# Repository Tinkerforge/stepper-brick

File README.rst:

Stepper Brick
=============

This repository contains the firmware source code and the hardware design
files. The documentation generator configs can be found at
https://github.com/Tinkerforge/generators

Repository Content
------------------

software/:
 * examples/: Examples for all supported languages
 * build/: Compiled files
 * src/: Source code of firmware
 * Makefile: Makefile to build project

hardware/:
 * Contains KiCad project files and additionally schematics as PDF

datasheets/:
 * Contains datasheets for sensors and complex ICs that are used

Hardware
--------

The hardware is designed with the open source EDA Suite KiCad
(http://www.kicad.org). Before you are able to open the files,
you have to install the Tinkerforge kicad-libraries
(https://github.com/Tinkerforge/kicad-libraries). You can either clone
them directly in hardware/ or clone them in a separate folder and
symlink them into hardware/
(ln -s kicad_path/kicad-libraries project_path/hardware). After that you
can open the .pro file in hardware/ with KiCad and from there view and
modify the schematics and the PCB layout.

Software
--------

If you want to do your own Brick/Bricklet firmware development we highly
recommend that you use our build environment setup script and read the
tutorial (https://www.tinkerforge.com/en/doc/Tutorials/Tutorial_Build_Environment/Tutorial.html).

To compile the C code we recommend you to install the newest GNU Arm Embedded
Toolchain (https://launchpad.net/gcc-arm-embedded/+download).
You also need to install bricklib (https://github.com/Tinkerforge/bricklib).

You can either clone it directly in software/src/ or clone it in a
separate folder and symlink it into software/src/
(ln -s bricklib_path/bricklib project_path/software/src/). Finally make sure to
have CMake installed (http://www.cmake.org/cmake/resources/software.html).

After that you can build the firmware by invoking make in software/.
The firmware (.bin) can then be found in software/build/ and uploaded
with brickv (click button "Flashing" on start screen).

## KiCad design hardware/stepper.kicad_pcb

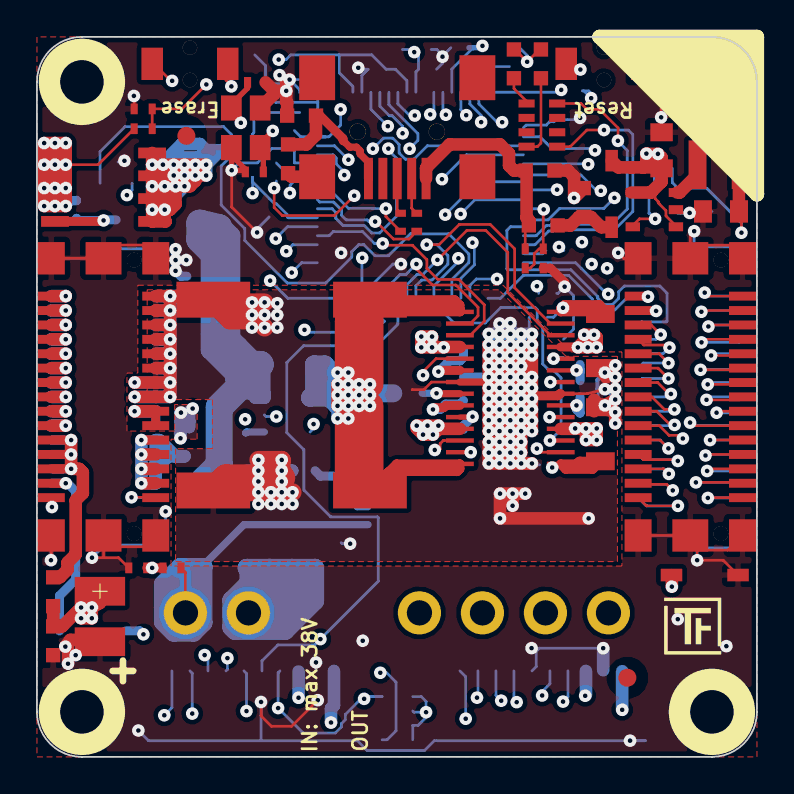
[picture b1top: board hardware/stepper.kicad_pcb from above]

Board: 4 copper layers, 40.0 x 40.0 mm, 107 parts (0 on the bottom side), 109 nets.

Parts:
C1, C2: 9pF; C0402
C3, C4, C5, C11, C14, C17, C20, C21, C22, C24, C25, C27, C28, C30, C32, C33: 100nF; C0402
C6, C8: 1nF; C0402
C7, C12, C13: 220nF; C0603
C9, C10: 330µF/50V; ELKO_103
C15: 100µF; 3528-21
C16, C18: 10µF; C0805
C19, C31: 4.7µF; C0603
C23: 2.2µF; C0603
C26: DNP; C0402
C29: 10µF/10V; C0805
C34, C35, C36: DNP; C0603
D1: blue; D0603
D2: red; D0603
D3: Z12V; SOD-123
D4, D5: PMEG4050BEP; SOD-128
D6, D7: B0520LW-7-F; SOD-123
D8: Z3.3V; SOD-123
FB1, FB2, FB3, FB4, FB5: FB; C0603
Fiducial_Mark: VAL**; Fiducial_Mark
Fiducial_Mark#2, Fiducial_Mark#3, Fiducial_Mark#4: VAL**; Fiducial_Mark
J1, J2, J3, J4: DRILL; DRILL_NP
J5: USB-MINI-B-SMD
J6, J8: STACK-UP-HIGH; BTB08-ACS-TOP
J7, J9: STACK-DOWN; BTB08-ACS-BTM
L1: NR3015T4R7M; NR3030
L2: LBR2012T100K; C0805
P1: black; OQ_2P
P2: green; OQ_4P
P3, P4: CON-SENSOR
Q1: FDS8449; SOIC-8-MOSFET
Q2: AO4421; SOIC-8-MOSFET
Q3: 2N7002; SOT23GDS
R1, R2: 27; R0402
R3: 1.8k; R0402
R4, R14: 2.7k; R0402
R5: FB; C0603
R6, R10, R12, R18: 10k; R0402
R7, R11, R13, R16, R22: 1k; R0402
R8: 10k; 0402
R9: 100k; R0402
R15, R19: 47k; R0402
R17: 0.01; R1206
R20, R21: 0.15; R1206
R23: 0; R0603
R24: DNP; R0603
R25: 1R0; R0402
RP1, RP2: 1k; 4X0603
SW1: Reset; TACT-SWITCH
SW2: Erase; TACT-SWITCH
U1: AT91SAM3SXB; LQFP64
U2: ZXCT1086; SOT23-5
U3: DRV8811PWP; HTSSOP28
U4: EUP3406; SOT23-5
VAL: WEEE_7mm
VAL#2: CE_5mm
X1: 16Mhz; CRYSTAL_3225

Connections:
3V3: C5.2, C16.1, C17.1, C19.1, C20.1, C21.1, C22.1, C26.1, C29.1, C30.1, C33.1, D1.1, D2.1, D6.1, D8.2, J6.20, L1.2, P3.3, P3.6, P4.3, R16.1, R23.1, RP2.1, RP2.2, RP2.3, RP2.4, SW2.2, U1.1, U1.7, U1.18, U1.45, U1.58, U2.5, U3.10
BRICKLET-I2C-SCL: P3.4, P4.4, RP2.5, U1.36
BRICKLET-I2C-SDA: P3.5, P4.5, RP2.8, U1.43
BRICKLET-IO0_0/AD0: P3.7, U1.3
BRICKLET-IO0_1: P3.8, U1.5
BRICKLET-IO0_2/PWM0: P3.9, U1.48
BRICKLET-IO0_3: P3.10, U1.25
BRICKLET-IO1_0/AD1: P4.7, U1.4
BRICKLET-IO1_1: P4.8, U1.6
BRICKLET-IO1_2/PWM1: P4.9, U1.47
BRICKLET-IO1_3: P4.10, U1.19
GND: C1.2, C2.2, C3.2, C4.2, C5.1, C15.2, C16.2, C17.2, C18.2, C19.2, C20.2, C21.2, C22.2, C23.2, C24.2, C25.2, C27.2, C28.2, C29.2, C30.2, C31.2, C32.2, C33.2, C34.2, C35.2, C36.2, D8.1, FB1.1, FB4.2, J6.EP, J7.EP, J8.EP, J9.EP, P3.2, P3.EP, P4.2, P4.6, P4.EP, R4.1, R5.2, R7.2, R11.2, R13.1, R24.2, SW1.2, U1.2, U1.17, U1.46, U1.60, U2.2, U4.2, X1.3
unnamed: C3.1, R12.1, R14.2, U3.8
unnamed: C6.1, R15.1, U3.6
unnamed: C7.2, U3.20
unnamed: C8.1, R19.1, U3.9
unnamed: C11.2, R20.1, U3.14
unnamed: C12.1, U3.23
unnamed: C12.2, U3.24
unnamed: C13.2, U3.22
unnamed: C14.1, R21.2, U3.1
unnamed: C23.1, C24.1, C25.1, C27.1, C28.1, L2.1, U1.8, U1.12, U1.24, U1.54
unnamed: C26.2, R23.2, R24.1, U4.5
unnamed: C31.1, R25.1
unnamed: C32.1, L2.2, R25.2, U1.64
unnamed: C35.1, FB3.2, J5.1, R3.1
unnamed: D1.2, RP1.1
unnamed: D2.2, RP1.4
unnamed: D3.2, Q1.G, R9.2
unnamed: D4.1, Q2.D
unnamed: D4.2, D5.2, R17.2, U2.3
unnamed: D5.1, P1.1, R9.1, R10.1
unnamed: D6.2, J8.28, J9.28
unnamed: FB1.2, FB2.1, J5.5
unnamed: FB2.2, J5.6
unnamed: FB4.1, J8.21, J8.23, J8.25, J8.27, J9.21, J9.23, J9.25, J9.27
unnamed: FB5.2, J8.22, J8.24, J8.26, J9.22, J9.24, J9.26
unnamed: J5.2, R1.1
unnamed: J5.3, R2.1
unnamed: J6.6, J7.8
unnamed: J6.7, J7.7, R22.1
unnamed: J6.8, J7.10
unnamed: J6.10, J7.12
unnamed: J6.12, J7.14
unnamed: J6.13, J7.13
unnamed: J6.14, J7.16
unnamed: J6.15, J7.15
unnamed: J6.16, J7.18
unnamed: J6.17, J7.17
unnamed: J6.18, J7.20
unnamed: J6.21, J7.21
unnamed: J6.22, J7.22
unnamed: J6.23, J7.23
unnamed: J6.24, J7.24
unnamed: J6.25, J7.25
unnamed: J6.27, J7.27
unnamed: J6.29, J7.29
unnamed: J6.30, J7.30
unnamed: J8.29, J9.29
unnamed: J8.30, J9.30
unnamed: L1.1, U4.3
unnamed: P1.2, Q1.D
unnamed: P2.1, U3.25
unnamed: P2.2, U3.4
unnamed: P2.3, U3.18
unnamed: P2.4, U3.11
unnamed: Q2.G, Q3.D, R8.1
unnamed: R1.2, U1.56
unnamed: R2.2, U1.57
unnamed: R18.2, U2.1
unnamed: RP1.5, U1.29
unnamed: RP1.8, U1.30
unnamed: SW2.1, U1.55
PWR-CUR-SENSE: R18.1, U1.10
PWR-DAC-1/5: R14.1, U1.31
PWR-DAC-DECAY: C4.1, U1.63, U3.5
PWR-DAC-VREF: R12.2, U1.59
PWR-DIR: U1.38, U3.3
PWR-ENABLE: R16.2, U1.15, U3.26
PWR-HOME: U1.35, U3.2
PWR-RESET: U1.52, U3.17
PWR-SLEEP: U1.23, U3.27
PWR-SR: U1.44, U3.16
PWR-STEP: U1.20, U3.19
PWR-USM0: U1.41, U3.13
PWR-USM1: U1.42, U3.12
PWR-VEXT: R10.2, R11.1, U1.13
PWR-VSTACK: R6.2, R7.1, U1.16
PWR-VSTACK-SW: Q3.G, R13.2, U1.37
STACK-DETECT/JTAG-TMS: J6.9, J7.9, U1.51
STACK-I2C-SCL/JTAG-TDO: J6.4, J7.4, U1.49
STACK-I2C-SDA/JTAG-TDI: J6.2, J7.2, U1.33
STACK-INT: J6.19, J7.19, U1.32
STACK-PGND: C6.2, C7.1, C8.2, C9.2, C10.2, C11.1, C14.2, D3.1, J8.1, J8.3, J8.5, J8.7, J8.9, J8.11, J8.13, J8.15, J8.17, J8.19, J9.1, J9.3, J9.5, J9.7, J9.9, J9.11, J9.13, J9.15, J9.17, J9.19, Q1.S, Q3.S, R5.1, R15.2, R19.2, R20.2, R21.1, U3.7, U3.21, U3.EP
STACK-PVCC: J8.2, J8.4, J8.6, J8.8, J8.10, J8.12, J8.14, J8.16, J8.18, J8.20, J9.2, J9.4, J9.6, J9.8, J9.10, J9.12, J9.14, J9.16, J9.18, J9.20, Q2.S, R6.1, R8.2
STACK-RESET: R22.2, SW1.1, U1.39
STACK-SER-RXD: J6.26, J7.26, U1.11
STACK-SER-TXD: J6.28, J7.28, U1.14
STACK-SPI-MISO: J6.1, J7.1, U1.27
STACK-SPI-MOSI: J6.3, J7.3, U1.22
STACK-SPI-SCLK: J6.5, J7.5, U1.21
STACK-SPI-SELECT: J7.6, U1.28
STACK-SYNC/JTAG-TCK: J6.11, J7.11, U1.53
USB-DETECT: R3.2, R4.2, U1.26
VPP: C9.1, C10.1, C13.1, R17.1, U2.4, U3.15, U3.28
VSTACK: C15.1, C18.1, C36.1, D7.2, FB5.1, P3.1, P4.1, U4.1, U4.4
VUSB: C34.1, D7.1, FB3.1
XIN: C2.1, U1.62, X1.2
XOUT: C1.1, U1.61, X1.1

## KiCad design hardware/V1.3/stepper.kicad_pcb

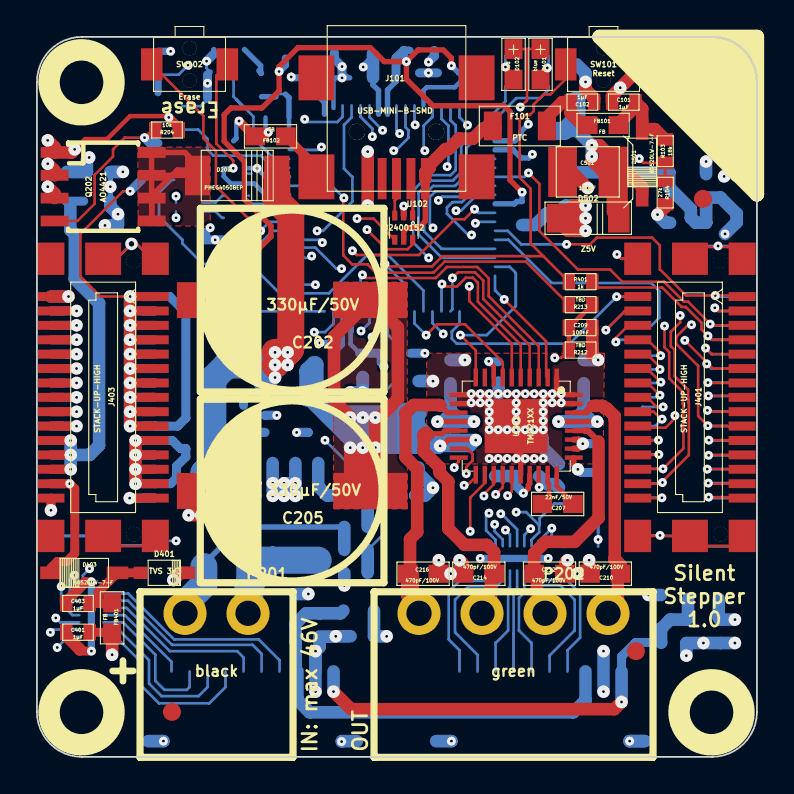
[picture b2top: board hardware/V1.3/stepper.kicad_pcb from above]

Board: 4 copper layers, 40.0 x 40.0 mm, 127 parts (0 on the bottom side), 128 nets.

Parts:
C101, C102, C301, C302, C303, C304, C401, C402, C403, C404: 1µF; 0402E
C103, C104: 9pF; 0402E
C201, C209, C217, C218, C503, C506, C507, C508, C510, C511, C512, C513, C515, C517, C518: 100nF; 0402E
C202, C205: 330µF/50V; ELKO_103
C203: 470nF; 0402E
C204, C505, C516: 4.7µF; 0603E
C206, C208, C211, C213: 100nF/50V; 0603E
C207: 22nF/50V; 0603E
C210, C212, C214, C216: 470pF/100V; 0603E
C215: 4.7µF/50V; 1206
C501: 100µF; 3528-21
C502, C504: 10µF; 0805
C509: 2.2µF; 0603E
C514: 10µF/10V; 0805
D101: blue; D0603E
D102: red; D0603E
D201: Z12V; SOD-123
D202, D203: PMEG4050BEP; SOD-128
D301, D402: ESD5V0D3B-TP; SOD-323
D302: ESD3V3D3B-TP; SOD-323
D401: TVS 3V3; SOD-323
D403, D501: B0520LW-7-F; SOD-123
D502: Z5V; MiniMelf
D503: Z3.3V; MiniMelf
F101: PTC; 1206
FB101, FB102, FB401, FB402: FB; 0603E
FB301, FB302: FILTER; 0603E
FILTER301, FILTER302: Filter-8x; DFN16-33x135
Fiducial_Mark: VAL**; Fiducial_Mark
Fiducial_Mark#2, Fiducial_Mark#3, Fiducial_Mark#4, Fiducial_Mark#5, Fiducial_Mark#6: VAL**; Fiducial_Mark
J101: USB-MINI-B-SMD
J102, J103, J104, J105: DRILL; DRILL_NP
J401, J403: STACK-UP-HIGH; BTB08-ACS-TOP
J402, J404: STACK-DOWN; BTB08-ACS-BTM
L101: 744230900; WE-CNSW-0603
L501: LBR2012T100K; 0805
P201: black; OQ_2P
P202: green; OQ_4P
P301, P302: CON-SENSOR
Q201: FDS8449; SOIC-8-MOSFET
Q202: AO4421; SOIC-8-MOSFET
Q203: 2N7002; SOT23GDS
R101, R102: 27; 0402E
R103: 18k; 0402E
R104: 27k; 0402E
R201: 0; 0603E
R202, R204, R206, R210: 10k; 0402E
R203, R207, R208, R401: 1k; 0402E
R205: 100k; 0402E
R209: 0.01; 1206
R211: 2R2; 0402E
R212, R213: TBD; 0402E
R214, R215: 0.12/0.5W; 1206
R501: 1R0; 0402E
RP101, RP301: 1k; 4X0603
SW101: Reset; TACT-SWITCH
SW102: Erase; TACT-SWITCH
U101: AT91SAM3SXB; LQFP64
U102: 82400152; SOT563-SPEC
U201: ZXCT1086; SOT23-5
U202: TMC21XX; QFN36_5X6
U501: LD1117; SOT-223
VAL: WEEE_7mm_back
VAL#2: CE_5mm
X101: 16Mhz; CRYSTAL_3225

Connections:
3V3: C201.2, C302.1, C401.1, C502.1, C503.1, C505.1, C506.1, C507.1, C508.1, C514.1, C515.1, C518.1, D101.1, D102.1, D503.2, FB302.1, FB401.1, FILTER302.14, J401.20, RP301.1, RP301.2, RP301.3, RP301.4, SW102.2, U101.1, U101.7, U101.18, U101.45, U101.58, U201.5, U202.8, U501.2
BRICKLET-I2C-SCL: FILTER301.16, FILTER302.16, RP301.8, U101.36
BRICKLET-I2C-SDA: FILTER301.15, FILTER302.15, RP301.5, U101.43
BRICKLET-IO0_0/AD0: FILTER301.10, U101.3
BRICKLET-IO0_1: FILTER301.11, U101.5
BRICKLET-IO0_2/PWM0: FILTER301.12, U101.48
BRICKLET-IO0_3: FILTER301.13, U101.25
BRICKLET-IO1_0/AD1: FILTER302.13, U101.4
BRICKLET-IO1_1: FILTER302.12, U101.6
BRICKLET-IO1_2/PWM1: FILTER302.11, U101.47
BRICKLET-IO1_3: FILTER302.10, U101.19
GND: C101.2, C102.2, C103.2, C104.2, C301.2, C302.2, C303.2, C304.2, C401.2, C402.2, C403.2, C404.2, C501.2, C502.2, C503.2, C504.2, C505.2, C506.2, C507.2, C508.2, C509.2, C510.2, C511.2, C512.2, C513.2, C514.2, C515.2, C516.2, C517.2, C518.2, D301.2, D302.2, D401.2, D402.2, D502.1, D503.1, FB102.1, FILTER301.14, FILTER301.EXP, FILTER302.EXP, J101.5, J401.EP, J402.EP, J403.21, J403.23, J403.25, J403.27, J403.EP, J404.21, J404.23, J404.25, J404.27, J404.EP, P301.2, P301.EP, P302.2, P302.EP, R104.1, R201.2, R203.2, R207.2, R208.1, SW101.2, U101.2, U101.17, U101.46, U101.60, U102.2, U201.2, U501.1, X101.3
M1: C216.2, P202.1, U202.13
M2: C214.2, P202.2, U202.15
M3: C212.2, P202.3, U202.32
M4: C210.2, P202.4, U202.34
unnamed: C102.1, F101.1, FB101.2
unnamed: C203.1, R211.1, U202.26
unnamed: C204.1, R211.2, U202.25
unnamed: C207.1, U202.27
unnamed: C207.2, U202.28
unnamed: C208.2, U202.29
unnamed: C209.2, R212.1, R213.2, U202.23
unnamed: C217.2, R214.2, U202.14
unnamed: C218.2, R215.2, U202.33
unnamed: C303.1, D301.1, FB301.2, P301.1, P302.1
unnamed: C304.1, D302.1, FB302.2, P301.3, P302.3
unnamed: C403.1, D401.1, D403.1, FB401.2
unnamed: C404.1, D402.1, FB402.2, J403.22, J403.24, J403.26, J404.22, J404.24, J404.26
unnamed: C509.1, C510.1, C511.1, C512.1, C513.1, L501.1, U101.8, U101.12, U101.24, U101.54
unnamed: C516.1, R501.1
unnamed: C517.1, L501.2, R501.2, U101.64
unnamed: D101.2, RP101.1
unnamed: D102.2, RP101.4
unnamed: D201.2, Q201.G, R205.2
unnamed: D202.1, Q202.D
unnamed: D202.2, D203.2, R209.2, U201.3
unnamed: D203.1, P201.1, R205.1, R206.1
unnamed: D403.2, J403.28, J404.28
unnamed: F101.2, J101.1, U102.5
unnamed: FB102.2, J101.6
unnamed: FILTER301.1, P301.4
unnamed: FILTER301.2, P301.5
unnamed: FILTER301.3, P301.6
unnamed: FILTER301.4, P301.10
unnamed: FILTER301.5, P301.9
unnamed: FILTER301.6, P301.8
unnamed: FILTER301.7, P301.7
unnamed: FILTER302.1, P302.4
unnamed: FILTER302.2, P302.5
unnamed: FILTER302.3, P302.6
unnamed: FILTER302.4, P302.7
unnamed: FILTER302.5, P302.8
unnamed: FILTER302.6, P302.9
unnamed: FILTER302.7, P302.10
unnamed: J101.2, U102.1
unnamed: J101.3, U102.3
unnamed: J401.6, J402.8
unnamed: J401.7, J402.7, R401.1
unnamed: J401.8, J402.10
unnamed: J401.10, J402.12
unnamed: J401.12, J402.14
unnamed: J401.13, J402.13
unnamed: J401.14, J402.16
unnamed: J401.15, J402.15
unnamed: J401.16, J402.18
unnamed: J401.17, J402.17
unnamed: J401.18, J402.20
unnamed: J401.21, J402.21
unnamed: J401.22, J402.22
unnamed: J401.23, J402.23
unnamed: J401.24, J402.24
unnamed: J401.25, J402.25
unnamed: J401.27, J402.27
unnamed: J401.29, J402.29
unnamed: J401.30, J402.30
unnamed: J403.29, J404.29
unnamed: J403.30, J404.30
unnamed: L101.1, R102.1
unnamed: L101.2, U102.4
unnamed: L101.3, U102.6
unnamed: L101.4, R101.1
unnamed: P201.2, Q201.D
unnamed: Q202.G, Q203.D, R204.1
unnamed: R101.2, U101.56
unnamed: R102.2, U101.57
unnamed: R210.2, U201.1
unnamed: RP101.5, U101.30
unnamed: RP101.8, U101.29
unnamed: SW102.1, U101.55
PWR-CS_CFG3: U101.32, U202.2
PWR-CUR-SENSE: R210.1, U101.10
PWR-DAC-VREF: R213.1, U101.59
PWR-DC0: U101.41, U202.17
PWR-DCEN_CFG4: U101.9, U202.18
PWR-DCIN_CFG5: U101.23, U202.19
PWR-DIAG0: U101.52, U202.20
PWR-DIAG1: U101.42, U202.21
PWR-DIR: U101.38, U202.7
PWR-ENABLE: U101.15, U202.22
PWR-SCK_CFG2: U101.44, U202.3
PWR-SD0_CFG0: U101.35, U202.5
PWR-SDI_CFG1: U101.34, U202.4
PWR-SPI_MODE: U101.31, U202.10
PWR-STEP: U101.20, U202.6
PWR-VEXT: R206.2, R207.1, U101.13
PWR-VSTACK: R202.2, R203.1, U101.16
PWR-VSTACK-SW: Q203.G, R208.2, U101.37
STACK-DETECT/JTAG-TMS: J401.9, J402.9, U101.51
STACK-I2C-SCL/JTAG-TDO: J401.4, J402.4, U101.49
STACK-I2C-SDA/JTAG-TDI: J401.2, J402.2, U101.33
STACK-INT: J401.19, J402.19, U101.63
STACK-PGND: C201.1, C202.2, C203.2, C204.2, C205.2, C206.2, C209.1, C210.1, C211.2, C212.1, C213.2, C214.1, C215.2, C216.1, C217.1, C218.1, D201.1, J403.1, J403.3, J403.5, J403.7, J403.9, J403.11, J403.13, J403.15, J403.17, J403.19, J404.1, J404.3, J404.5, J404.7, J404.9, J404.11, J404.13, J404.15, J404.17, J404.19, Q201.S, Q203.S, R201.1, R212.2, R214.1, R215.1, U202.1, U202.11, U202.12, U202.24, U202.35, U202.36, U202.EXP
STACK-PVCC: J403.2, J403.4, J403.6, J403.8, J403.10, J403.12, J403.14, J403.16, J403.18, J403.20, J404.2, J404.4, J404.6, J404.8, J404.10, J404.12, J404.14, J404.16, J404.18, J404.20, Q202.S, R202.1, R204.2
STACK-RESET: R401.2, SW101.1, U101.39
STACK-SER-RXD: J401.26, J402.26, U101.11
STACK-SER-TXD: J401.28, J402.28, U101.14
STACK-SPI-MISO: J401.1, J402.1, U101.27
STACK-SPI-MOSI: J401.3, J402.3, U101.22
STACK-SPI-SCLK: J401.5, J402.5, U101.21
STACK-SPI-SELECT: J402.6, U101.28
STACK-SYNC/JTAG-TCK: J401.11, J402.11, U101.53
USB-DETECT: R103.2, R104.2, U101.26
VEE: C202.1, C205.1, C206.1, C208.1, C211.1, C213.1, C215.1, R209.1, U201.4, U202.16, U202.30, U202.31
VSTACK: C301.1, C402.1, C501.1, C504.1, D501.2, D502.2, FB301.1, FB402.1, U501.3
VUSB: C101.1, D501.1, FB101.1, R103.1
XIN: C104.1, U101.62, X101.2
XOUT: C103.1, U101.61, X101.1

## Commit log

2011-08-25 initial hardware source commit
2011-08-25 add project description
2011-08-25 change voltage epsilon from 200mV to 1000mV
2011-08-26 remove adc tc, periodic conversion now done in bricklib with freerun
2011-08-26 change diode PMEG1020EH -> B0520LW-7-F
2011-08-31 fix typo in examples
2011-09-06 add red led error status code
2011-09-08 use voltage epsilon to switch between external and stack voltage
2011-09-08 compare external voltage for switching between external and stack voltage
2011-09-08 1/8 step default (instead of full step)
2011-09-08 fix bugs in acceleration calculation
2011-09-13 add java bindings and examples
2011-09-14 limit line length of java examples to 100 characters
2011-09-26 Add C# examples and bindings
2011-10-05 new ipcon version and fix typo
2011-10-05 Remove Bindings and IP Connection (these are generated and they change too often) and rename bindings to examples
2011-10-05 add tinkerforge package to python imports
2011-10-06 remove faulty gcc commandline invocation
2011-10-06 add firmware version and name
2011-12-15 remove debugging
2012-01-02 add code for voltage divider to allow motor currents below 500mA
2012-01-02 add changelog
2012-02-13 checkin of version 1.1: - remove driver power diodes - add fiducials - add version number in schematics
2012-02-14 add compatability for different tick types
2012-02-15 Add changelog entry
2012-02-20 fix wrong capactior value
2012-03-05 Fix bug with timeouts on windows (through bricklib)
2012-03-11 Fix bug with ADC calibration readout (through bricklib)
2012-04-03 add averaging for current measurement
2012-04-25 Unify capitalization of "IP connection" in examples
2012-04-27 Add sync rect API
2012-04-27 Update version for sync rect change
2012-05-09 Add PHP examples
2012-05-14 java: Remove unnecessary new String(...) calls
2012-05-25 Add Ruby examples
2012-06-05 Fix register_callback syntax error in Ruby examples on Windows
2012-06-12 Prefer IPConnection destroy over join_thread
2012-06-29 Add get_temperature and reset function (through bricklib)
2012-07-01 Add generate_makefile.bat for windows
2012-07-02 update to newest cmsis core_m3 files (through bricklib)
2012-07-02 Add usb hotplug support (through bricklib)
2012-07-02 Add time base API
2012-07-03 Add time base API, add all data function and callback, add state callback
2012-07-24 Stop state machine after disable call, don't drive if max velocity = 0
2012-07-24 Stop completely if max velocity is set to 0 while in drive mode
2012-07-25 Add Delphi example
2012-07-25 Fix callback signature in C/C++ example
2012-07-27 update firmware version
2012-08-08 delphi: Add comment about UID
2012-09-07 Ignore temporary build files
2012-10-08 Fix typo in changelog
2012-10-10 Remove unused define
2012-10-17 Add hardware name for compatibility with new bricklib
2012-10-24 Make cmake find the correct objcopy binary
    On some systems cmake uses the wrong objcopy binary, tell it to use
    the correct one.
2012-10-26 hange Bricklet Context size from 250 to 256 (through bricklib)
2012-11-13 Support for protocol 2.0
2012-11-22 Add compatability to newest bricklib version
2012-11-22 Reenumerate after USB reconnect
2012-11-29 Make Python examples compatible to Protocol V2.0
2012-11-29 Make Ruby examples Protocol 2.0 compatible
2012-11-29 Make C examples Protocol 2.0 compatible
2012-11-29 Make Java examples Protocol 2.0 compatible
2012-11-29 Make PHP examples Protocol 2.0 compatible
2012-11-29 Make Delphi/Pascal examples Protocol 2.0 compatible
2012-11-30 Add invalid parameter check to set_step_mode
2012-11-30 delphi: Remove unnecessary parentheses and call destructor again
2012-12-05 Add protocol 2.0 compatability to C# bindings
2012-12-06 Fix C example
2012-12-07 Fix Java example
2012-12-11 Avoid g++ warnings about missing casts in C examples
2012-12-13 Use user data parameter in PHP example
2013-01-09 Use specific device object for callbacks
2013-01-14 Adapt Java examples to latest IP Connection API
2013-01-16 Update Java example and use a final local instead of a global static variable
2013-01-17 Make Java examples compatible to new listener approach
2013-01-23 Add missing header to minimum voltage setter
2013-02-07 Use IPconnection disconnect explicitly in examples
2013-02-18 Add Visual Basic .NET examples
2013-02-22 Update Java example
2013-04-11 Add watchdog timer (restart after 16s of "deadlock")
2013-04-11 Remove redefinition of BRICK_FIRMWARE_VERSION_REVISION
2013-05-28 Fix bug in under voltage callback definition (wrong FID)
2013-06-27 Use tick_task to detect usb connect/disconnect instead of interrupt (through bricklib)
2013-08-13 Add shell examples
2013-08-14 shell: Shorten long lines in example
2013-08-21 windows: Don't trigger a build in generate_makefile.bat
    Also use normal make instead of a special named one.
2014-01-10 Add Perl examples
2014-01-14 perl: Fix warning about unsharing the $stepper variable
2014-01-15 php: Use const for constant values
2014-02-07 Add Mathematica examples
2014-02-10 perl: fixed namespace
2014-02-11 javascript: adding examples
2014-02-11 javascript: short examples
2014-02-18 javascript: examples fixed
2014-02-20 javascript: added comment
2014-02-20 javascript: add html example
2014-02-24 javascript: port 4280, startExample()
2014-02-28 javascript: Break long lines and cleanup whitespace
2014-03-05 Add LabVIEW examples
2014-03-06 labview: Add examples in LV2010 format
2014-03-25 matlab: adding examples
2014-03-28 perl: Fix warning
2014-04-02 java: Unify constants style
2014-04-02 perl: Unify print style
2014-04-17 matlab: Adapt examples to new callback style
2014-04-17 matlab: Add parentheses to make pygments happy
2014-06-12 change voltage divider resistor values for usb detect
2014-07-01 Add flag to compile with SPI stack DMA protocol (currently deactivated by default)
2014-07-07 Remove USB hotplug support (through bricklib)
2014-07-15 java: Replace System.console() usage with an Eclipse compatible pattern
2014-11-25 Use new SPI protocol
2014-11-25 Add changelog for v2.3.0
2014-12-02 Use ReadLine instead of ReadKey for C# example
2015-02-13 vbnet: Use ReadLine instead of ReadKey
    Because ReadKey doesn't work with a pipe as stdin on the RED Brick.
2015-03-02 windows: Stop cmake from searching for mingw32-make.exe
    Using MinGW Makefiles as generator makes cmake search for mingw32-make.exe
    which might not be installed because GnuWin32's make.exe is used instead.
2015-04-09 c: Whitespace
2015-05-19 Update state if only one step is set
2015-05-19 Add changelog, increase version to 2.3.1
2015-06-24 fix library configuration
2015-06-24 new stepper prototype, copy from last version, add filtering
2015-06-24 javascript: Clean up output creation
2015-06-24 schematic finished, board added
2015-06-24 remove old parts, place important components to pcb
2015-06-30 change step down to ldo, pcb: partially placement
2015-07-08 placement finished
2015-07-08 previous commit was uncomplete. parts placement finished
2015-07-09 changed placement
2015-07-25 Make JavaScript browser example textarea readonly
2015-07-28 Cleanup C/C++, C#, Java, Python and Ruby examples
2015-07-28 partial routing
2015-07-29 Reformat changelog
2015-07-30 Cleanup C/C++, C#, Java, Python and Ruby configuration examples
2015-08-07 Use full device class name in Python examples
2015-08-12 Fix minor warnings in C/C++ examples
2015-08-14 Cleanup Delphi examples
2015-08-18 Cleanup VB.NET examples
2015-08-19 Cleanup Perl examples
2015-08-25 partially routed
2015-08-26 change 0402, 0603 footprints to extended versions, fix placement
2015-08-26 fix placement, no drc errors
2015-08-26 add power routing
2015-08-27 more power routing
2015-08-27 routing improved
2015-08-27 routable, no drc errors
2015-08-27 change power routing
2015-08-28 fix power diode position
2015-08-28 fully routed, fine tuning missing
2015-08-28 fully routed, logos etc. placed, finished
2015-08-28 ordered version
2015-08-28 add voltage hint
2015-08-31 fix outer layer signal distance
2015-08-31 fix routing, change name to silent stepper brick
2015-09-09 Duplicate cmake call to fix bug during cmake creation
2015-09-14 increase external detection voltage
2015-09-15 move to own repository: silent-stepper-brick
2015-09-17 Add changelog and version define for 2.3.2
2015-09-30 Generator based example cleanup
2015-11-12 matlab: Fix callback handling for R2014a
    http://undocumentedmatlab.com/blog/matlab-callbacks-for-java-events-in-r2014a
2015-11-25 Include date and commit into changelog
2016-05-18 c: Add missing device destroy call
2016-06-29 Whitespace
2016-07-01 Make the change UID comment more explicit
2016-08-29 Make sure to use all chunks when writing firmware
    Change through Bricklib
2016-08-30 Fix changelog date
2016-12-05 Add ringbuffer and system timer utility as well as co_mcu support files to Makefile (all added through bricklib)
2017-01-06 Add COM_MESSAGE_USER_LAST_FID define (needed for newest bricklib)
2017-04-13 csharp: Adapt example
2017-04-19 Whitespace in examples
2017-04-19 perl: Fix example logic
2017-04-20 shell: Adapt example
2017-05-11 Add support for co-mcu Bricklets
2017-05-11 Add ref for last changelog entry
2017-05-12 Add most of the 3d information (tbc)
    Connectors are missing
2017-05-12 python: Add missing callback parameter
2017-06-02 octave: Use javaObject instead of deprecated java_new
2017-06-02 java: Whitespace
2017-06-09 Add missing 3d information
2017-06-09 Add 3d model (*.step and *.FCStd)
2017-06-16 Add heatsink and new switches to 3d model
2017-06-16 Fix orientation of diodes
2017-06-16 Add heatsink to 3d model
2017-06-28 Update changelog and version
2017-06-28 Add tag ref to changelog
2017-11-30 Update examples from generator
2017-12-05 Remove initial USB enumeration (now done in bricklib)
2017-12-05 Increase firmware version, update changelog
2017-12-07 mathematica: Also generate .nb files
2017-12-12 Remove unused include
2017-12-12 Remove unused variable
2017-12-13 Add date and ref to changelog
2018-01-11 Increase version number (message duplication bug fix through bricklib)
2018-01-11 Add ref to changelog
2018-02-19 javascript: Close div tag correctly
2018-02-20 Cleanup KiCad libraries config
    Ensure LibDir=kicad-libraries and LibName1=tinkerforge.
    Remove special library.
2018-04-27 Update version and changelog
2018-04-27 Add git ref to changelog
2018-05-24 perl: Use strict in examples
2018-05-29 Minor example tweaks
2018-07-11 Add Makefile with docker support
2018-07-11 Remove obsolete generate_makefile scripts
2018-07-11 Update directory structure and build instructions
2018-07-25 Add new 3d model
2018-07-31 Increase version and update changelog
2018-07-31 Update changelog ref
2018-09-03 Unify spelling in changelog
2018-11-06 Add rust examples
2018-11-07 rust: Accept host names for ip connection, fix naming inconsistencies
2018-11-07 rust: Rename callback receivers.
2018-12-14 Add go examples.
2018-12-18 go: Change import path.
2018-12-18 go: Change import path again.
2018-12-20 rust: Reformat examples.
2019-01-24 mqtt: Add examples.
2019-01-24 mqtt: Fix example header.
2019-01-24 mqtt: Remove executable bit in example permissions.
2019-01-24 go: Minor example fixes.
2019-01-24 mqtt: Minor example fixes.
2019-02-27 Increase version for new release (changes in bricklib)
2019-02-27 Add rev to changelog
2019-05-14 Update rust examples.
2019-08-22 c: Adapt to bindings changes
2020-01-13 examples: Use python3 input instead of python2 raw_input.
2020-01-13 examples: mqtt: Remove trailing whitespace.
2020-01-14 examples: Use python3 input by default.
2020-03-18 rust: Update to new skeleton
2020-03-19 examples: Properly stop motor before disabling motor power
    Disabling motor power while motor is still running could cause
    hardware damage.
2020-04-07 examples: Add missing imports for sleep calls
2020-04-07 examples: rust: Always block when calling bindings functions.
2020-04-07 examples: rust: Block when calling bindings functions.
2021-10-25 Update KiCad link
    https://www.kicad.org/blog/2021/10/Avoid-links-to-former-kicad-domain/
2022-07-06 Add license files.
2024-02-21 examples/rust: Fix random number generation.

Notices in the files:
hardware/V1.3/stepper.kicad_pcb:
Licensed under CERN OHL v.1.1
Copyright (©) 2015, B.Nordmeyer
Copyright Tinkerforge GmbH 2015.
This documentation describes Open Hardware and is licensed under the
CERN OHL v. 1.1.
hardware/stepper.kicad_pcb:
Copyright (©) 2013, B.Nordmeyer
Copyright Tinkerforge GmbH 2013.
